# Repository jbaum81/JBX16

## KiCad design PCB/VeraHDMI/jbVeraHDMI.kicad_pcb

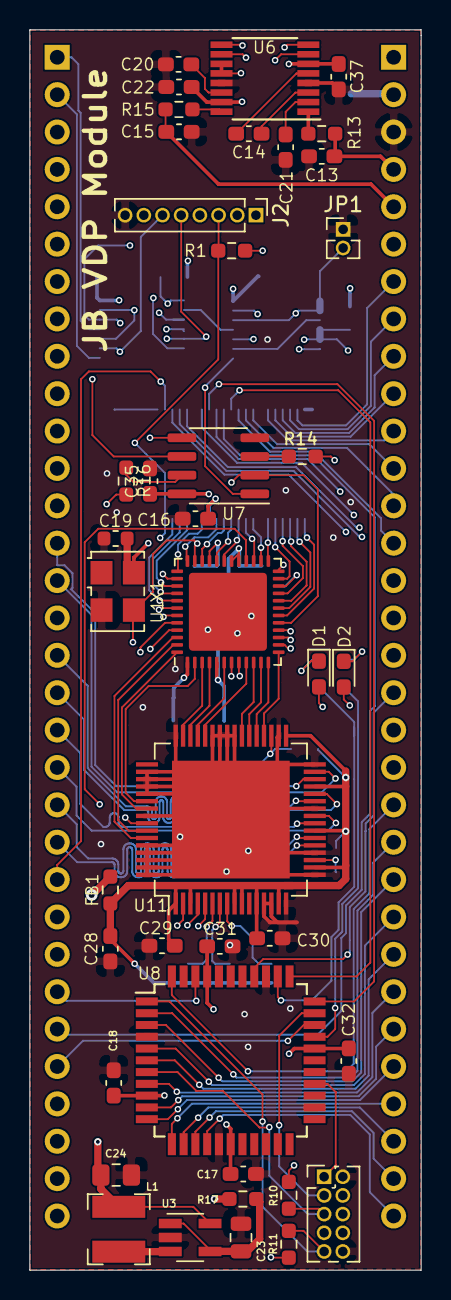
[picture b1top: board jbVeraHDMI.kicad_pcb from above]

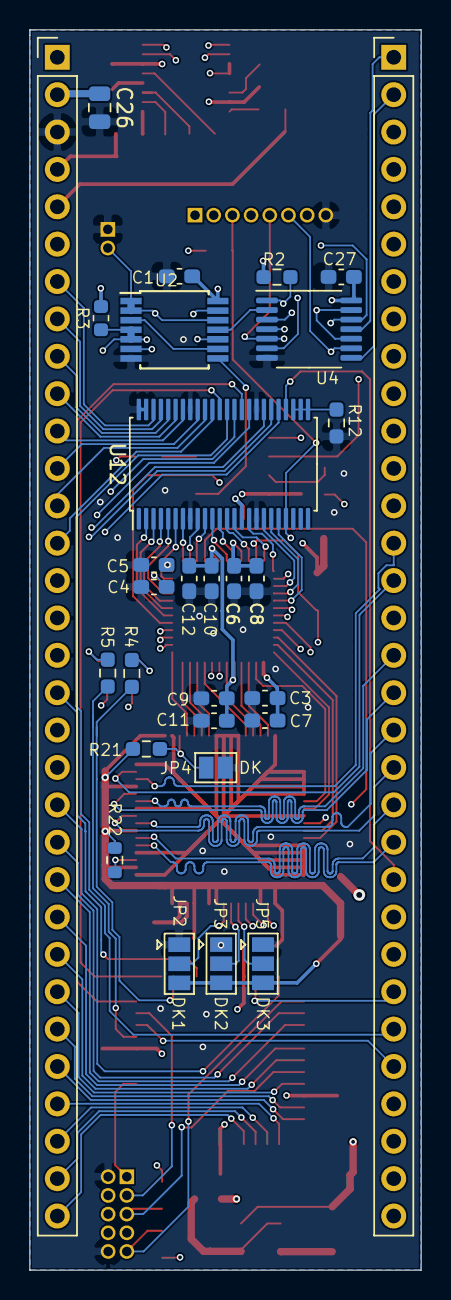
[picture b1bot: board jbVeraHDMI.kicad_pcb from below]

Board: 4 copper layers, 26.6 x 84.3 mm, 70 parts (29 on the bottom side), 119 nets.

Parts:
C1, C3, C4, C5, C6, C9, C10, C16, C17, C18, C27, C31, C32, C35: 100nF; C_0603_1608Metric_Pad1.08x0.95mm_HandSolder
C7, C8, C11, C12, C22, C37: 4.7uF; C_0603_1608Metric_Pad1.08x0.95mm_HandSolder
C13, C15: 2.7nF; C_0603_1608Metric_Pad1.08x0.95mm_HandSolder
C14: 1u; C_0603_1608Metric_Pad1.08x0.95mm_HandSolder
C19: 100nF; C_0603_1608Metric
C20: 2.2uF; C_0603_1608Metric_Pad1.08x0.95mm_HandSolder
C21: 1uF; C_0603_1608Metric_Pad1.08x0.95mm_HandSolder
C23, C26: 10uF; C_0805_2012Metric
C24: 10uF; C_0805_2012Metric_Pad1.18x1.45mm_HandSolder
C28: 10uF; C_0603_1608Metric_Pad1.08x0.95mm_HandSolder
C29, C30: .1uF; C_0603_1608Metric_Pad1.08x0.95mm_HandSolder
D1: RED; LED_0603_1608Metric_Pad1.05x0.95mm_HandSolder
D2: GREEN; LED_0603_1608Metric_Pad1.05x0.95mm_HandSolder
FB1: 600R; R_0603_1608Metric_Pad0.98x0.95mm_HandSolder
J2: Prog; PinHeader_1x08_P1.27mm_Vertical
J4: MercuryII-L; PinHeader_1x32_P2.54mm_Vertical
J5: MercuryII-R; PinHeader_1x32_P2.54mm_Vertical
J7: JTAG; PinHeader_2x05_P1.27mm_Vertical
JP1: Flash enable; PinHeader_1x02_P1.27mm_Vertical
JP2: DK1; SolderJumper-3_P1.3mm_Open_Pad1.0x1.5mm
JP3: DK2; SolderJumper-3_P1.3mm_Open_Pad1.0x1.5mm
JP4: DK; SolderJumper-2_P1.3mm_Open_Pad1.0x1.5mm
JP5: DK3; SolderJumper-3_P1.3mm_Open_Pad1.0x1.5mm
L1: NRS4018T2R2MDGJ; L_Bourns-SRN4018
R1, R2: 10k; R_0603_1608Metric_Pad0.98x0.95mm_HandSolder
R3: 10k; R_0603_1608Metric
R4, R5: 1K; R_0603_1608Metric_Pad0.98x0.95mm_HandSolder
R10, R11, R12, R21: 10K; R_0603_1608Metric_Pad0.98x0.95mm_HandSolder
R13, R15: 560; R_0603_1608Metric_Pad0.98x0.95mm_HandSolder
R14, R16: 47k; R_0603_1608Metric_Pad0.98x0.95mm_HandSolder
R17: 1; R_0603_1608Metric_Pad0.98x0.95mm_HandSolder
R22: 500R; R_0603_1608Metric
U1: ICE40UP5K-SG48ITR50; QFN-48-1EP_7x7mm_P0.5mm_EP5.3x5.3mm
U2: 74AHC00PW; TSSOP-14_4.4x5mm_P0.65mm
U3: LTC3406BES5-1.2; SOT-23-5_HandSoldering
U4: 74CBTLV3126PW,118; TSSOP-14_4.4x5mm_P0.65mm
U6: WM8524CGEDT; TSSOP-16_4.4x5mm_P0.65mm
U7: W25Q16JVSNIQ; SOIC-8_3.9x4.9mm_P1.27mm
U8: ATF1502AS-xAx44; TQFP-44_10x10mm_P0.8mm
U11: TFP410PAP; HTQFP-64-1EP_10x10mm_P0.5mm_EP8x8mm
U12: SN74CB3T16210; TSSOP-48_6.1x12.5mm_P0.5mm
X1: SG5032CAN_25.000000M-TJGA3; Oscillator_SMD_SeikoEpson_SG8002LB-4Pin_5.0x3.2mm

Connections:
+1V2: C9.1, C10.1, C11.1, C12.1, C24.1, L1.2, U1.5, U1.29, U1.30, U3.5
+3V3: C1.1, C3.1, C4.1, C5.1, C6.1, C7.1, C8.1, C16.1, C19.1, C22.1, C26.1, C27.1, C35.1, C37.1, FB1.2, J5.2, R1.1, R2.1, R3.1, R14.1, R16.1, U1.1, U1.22, U1.24, U1.33, U2.14, U4.14, U6.6, U6.11, U6.12, U6.15, U7.8, U12.15, X1.4
+5V: C17.1, C18.1, C31.1, C32.1, D1.2, D2.2, J2.1, J5.1, J7.4, R10.1, R11.1, R17.2, U8.9, U8.17, U8.29, U8.41
AUDIO_BCK: U1.38, U6.9
AUDIO_DATA: U1.42, U6.7
AUDIO_LRCK: U1.43, U6.8
BUS_A0: U1.40, U12.19
BUS_A0_5V: J5.15, U12.30
BUS_A1: U1.39, U12.18
BUS_A1_5V: J5.16, U12.31
BUS_A2: U1.37, U12.16
BUS_A2_5V: J5.17, U12.33
BUS_A3: U1.41, U12.20
BUS_A3_5V: J5.20, U12.29
BUS_A4: U1.34, U12.13
BUS_A4_5V: J5.21, U8.44, U12.35
BUS_A5_5V: J5.22, U8.2
BUS_A6_5V: J5.23, U8.3
BUS_A7_5V: J5.24, U8.5
BUS_A8_5V: J5.25, U8.6
BUS_A9_5V: J5.26, U8.8
BUS_A10_5V: J5.27, U8.10
BUS_A11_5V: J5.28, U8.11
BUS_A12_5V: J5.29, U8.12
BUS_A13_5V: J5.30, U8.13
BUS_A14_5V: J5.31, U8.14
BUS_A15_5V: J5.32, U8.15
BUS_D0: U1.27, U12.10
BUS_D0_5V: J5.14, U12.38
BUS_D1: U1.26, U12.9
BUS_D1_5V: J5.13, U12.39
BUS_D2: U1.25, U12.7
BUS_D2_5V: J5.12, U12.40
BUS_D3: U1.23, U12.6
BUS_D3_5V: J5.11, U12.42
BUS_D4: U1.21, U12.5
BUS_D4_5V: J5.10, U12.43
BUS_D5: U1.20, U12.4
BUS_D5_5V: J5.9, U12.44
BUS_D6: U1.19, U12.3
BUS_D6_5V: J5.8, U12.45
BUS_D7: U1.18, U12.2
BUS_D7_5V: J5.7, U12.46
BUS_IRQ#: U1.32, U12.12
BUS_IRQ#_5V: J4.27, U12.36
BUS_RD#: U1.36, U12.14
BUS_RD#_5V: U8.33, U12.34
BUS_RES#_5V: J4.23, U12.28
BUS_RWB_5V: J4.26, U8.42
BUS_WR#: U1.31, U12.11
BUS_WR#_5V: U8.34, U12.37
D0+: J4.20, U11.25
D0-: J4.19, U11.24
D1+: J4.18, U11.28
D1-: J4.17, U11.27
D2+: J4.15, U11.31
D2-: J4.14, U11.30
DATDD: J4.28, U8.31
DVI33: C28.1, C29.1, C30.1, FB1.1, JP2.3, JP3.3, JP5.3, R21.2, R22.1, U11.1, U11.3, U11.9, U11.10, U11.12, U11.15, U11.18, U11.23, U11.29, U11.33
FLASH_SSEL_N: U2.8, U7.1
FPGA_CDONE: J2.2, JP1.2, R2.2, U1.7, U2.1, U2.2, U2.12, U4.1, U4.4, U4.10, U4.13
FPGA_CRESET_B: J2.3, R1.2, U1.8, U12.21
GND: C1.2, C3.2, C4.2, C5.2, C6.2, C7.2, C8.2, C9.2, C10.2, C11.2, C12.2, C13.2, C15.2, C16.2, C17.2, C18.2, C19.2, C20.2, C21.2, C22.2, C23.2, C24.2, C26.2, C27.2, C28.2, C29.2, C30.2, C31.2, C32.2, C35.2, C37.2, J2.8, J5.3, J7.2, J7.10, JP1.1, JP2.1, JP3.1, JP4.2, JP5.1, R12.1, U1.49, U2.7, U3.2, U4.7, U6.4, U6.13, U7.4, U8.4, U8.16, U8.24, U8.36, U11.13, U11.14, U11.16, U11.17, U11.20, U11.26, U11.32, U11.34, U11.40, U11.41, U11.42, U11.43, U11.48, U11.50, U11.51, U11.52, U11.53, U11.56, U11.60, U11.61, U11.62, U11.63, U11.64, U11.65, U12.8, U12.17, U12.32, U12.41, U12.47, U12.48, X1.2
L_AUDIO: C13.1, J5.4, R13.1
unnamed: C14.1, U6.3
unnamed: C14.2, U6.5
unnamed: C20.1, U6.14
unnamed: C21.1, U6.2
unnamed: C23.1, R17.1, U3.1, U3.4
unnamed: D1.1, R4.1
unnamed: D2.1, R5.1
unnamed: JP2.2, U11.8
unnamed: JP3.2, U11.7
unnamed: JP4.1, R21.1, U11.35
unnamed: JP5.2, U11.6
unnamed: L1.1, U3.3
unnamed: R12.2, U12.25, U12.26, U12.27
unnamed: R13.2, U6.1
unnamed: R14.2, U7.3
unnamed: R15.2, U6.16
unnamed: R16.2, U7.7
unnamed: R22.2, U11.19
unnamed: U2.3, U2.9
unnamed: U2.6, U2.10, U2.13
RDLED: R5.2, U8.30
R_AUDIO: C15.1, J5.5, R15.1
SD_MISO: J4.1, U4.11
SD_MOSI: J4.3, U4.6
SD_SCK: J4.2, U4.8
SD_SSEL: J4.4, U4.3
SD_SSEL_N: U2.11, U4.2
SPI_MISO: J2.4, U1.17, U4.12, U7.2
SPI_MOSI: J2.5, U1.14, U4.5, U7.5
SPI_SCK: J2.6, U1.15, U4.9, U7.6
SPI_SSEL_N: J2.7, R3.2, U1.16, U2.4, U2.5
SYSCLK: U1.35, U6.10, U11.57, X1.3
TCK: J7.1, U8.26
TDI: J7.9, R11.2, U8.1
TDO: J7.3, U8.32
TMS: J7.5, R10.2, U8.7
VGA_B0: U1.46, U11.59
VGA_B1: U1.47, U11.58
VGA_B2: U1.48, U11.55
VGA_B3: U1.2, U11.54
VGA_DE: U1.28, U11.2
VGA_G0: U1.3, U11.47
VGA_G1: U1.4, U11.46
VGA_G2: U1.6, U11.45
VGA_G3: U1.9, U11.44
VGA_HSYNC: U1.44, U11.4
VGA_R0: U1.10, U11.39
VGA_R1: U1.11, U11.38
VGA_R2: U1.12, U11.37
VGA_R3: U1.13, U11.36
VGA_VSYNC: U1.45, U11.5
WRLED: R4.2, U8.35
clk+: J4.21, U11.22
clk-: J4.22, U11.21
cpuClk: J5.18, U8.37

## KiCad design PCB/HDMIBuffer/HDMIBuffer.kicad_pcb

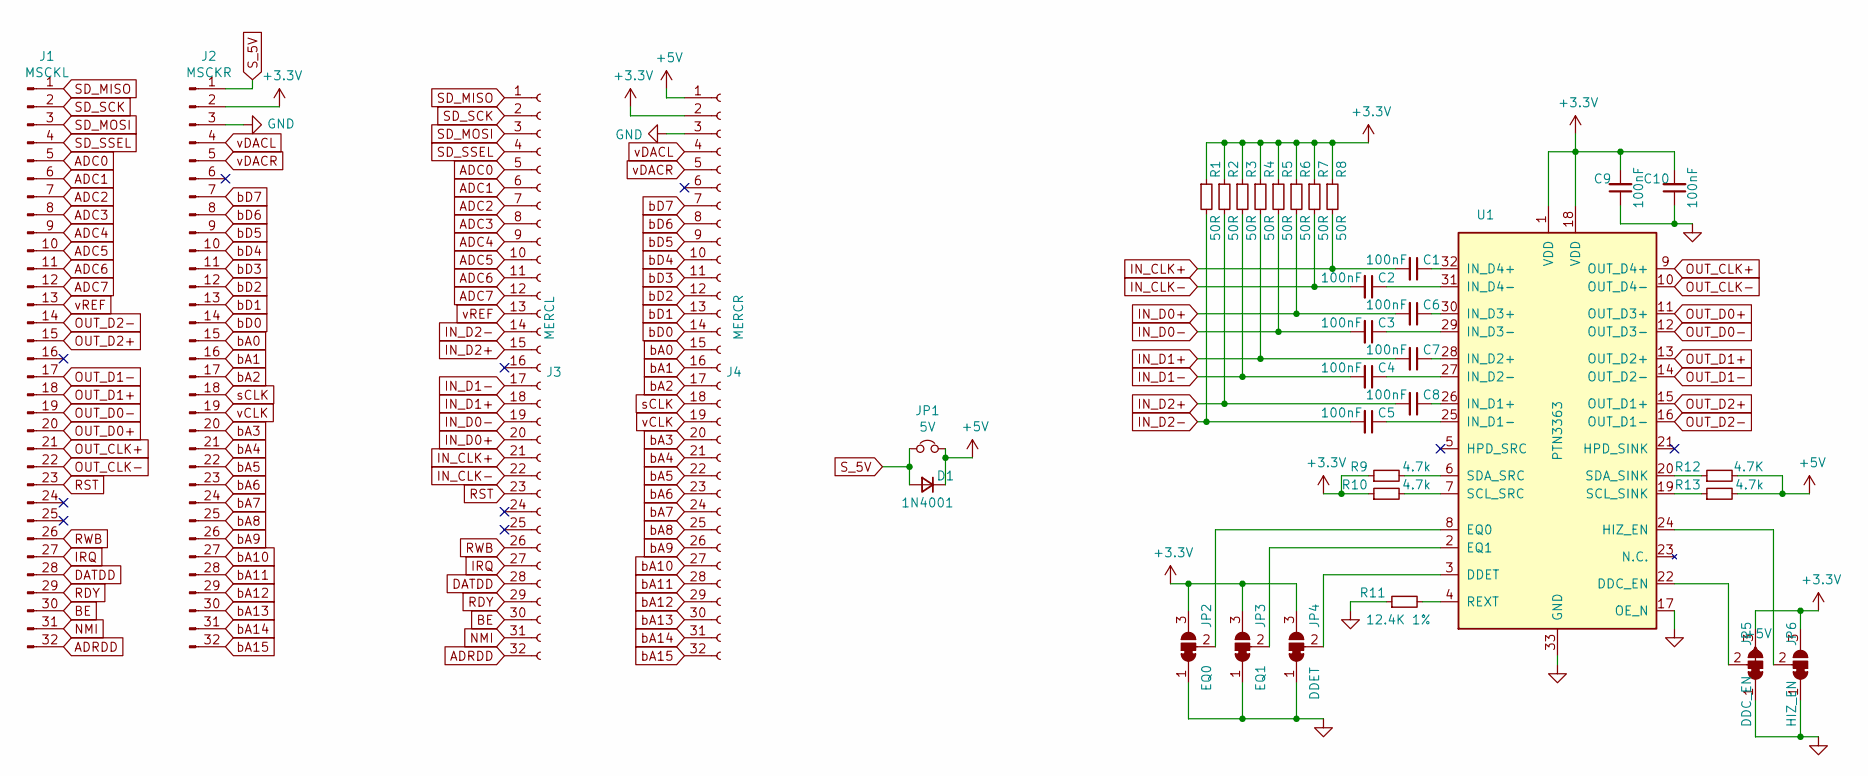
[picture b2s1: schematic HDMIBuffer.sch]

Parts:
C1, C2, C3, C4, C5, C6, C7, C8, C9, C10: 100nF; C_0603_1608Metric_Pad1.08x0.95mm_HandSolder
D1: 1N4001; D_0805_2012Metric
J1: MSCKL; PinHeader_1x32_P2.54mm_Vertical
J2: MSCKR; PinHeader_1x32_P2.54mm_Vertical
J3: MERCL; PinSocket_1x32_P2.54mm_Vertical
J4: MERCR; PinSocket_1x32_P2.54mm_Vertical
JP1: 5V; SolderJumper-2_P1.3mm_Open_Pad1.0x1.5mm
JP2: EQ0; SolderJumper-3_P1.3mm_Bridged12_Pad1.0x1.5mm_NumberLabels
JP3: EQ1; SolderJumper-3_P1.3mm_Bridged12_Pad1.0x1.5mm_NumberLabels
JP4: DDET; SolderJumper-3_P1.3mm_Bridged12_Pad1.0x1.5mm_NumberLabels
JP5: DDC_EN; SolderJumper-3_P1.3mm_Bridged12_Pad1.0x1.5mm_NumberLabels
JP6: HIZ_EN; SolderJumper-3_P1.3mm_Bridged12_Pad1.0x1.5mm_NumberLabels
R1, R2, R3, R4, R5, R6, R7, R8: 50R; R_0603_1608Metric_Pad0.98x0.95mm_HandSolder
R9, R10, R13: 4.7k; R_0603_1608Metric_Pad0.98x0.95mm_HandSolder
R11: 12.4K 1%; R_0603_1608Metric_Pad0.98x0.95mm_HandSolder
R12: 4.7K; R_0603_1608Metric_Pad0.98x0.95mm_HandSolder
U1: PTN3363; TQFN-32-1EP_5x5mm_P0.5mm_EP2.1x2.1mm_ThermalVias

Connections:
+3V3: C9.2, C10.2, J2.2, J4.2, JP2.3 (B), JP3.3 (B), JP4.3 (B), JP5.3 (B), JP6.3 (B), R1.1, R2.1, R3.1, R4.1, R5.1, R6.1, R7.1, R8.1, R9.1, R10.1, U1.1 (VDD), U1.18 (VDD)
+5V: D1.1 (K), J4.1, JP1.2, R12.2, R13.2
ADC0: J1.5, J3.5
ADC1: J1.6, J3.6
ADC2: J1.7, J3.7
ADC3: J1.8, J3.8
ADC4: J1.9, J3.9
ADC5: J1.10, J3.10
ADC6: J1.11, J3.11
ADC7: J1.12, J3.12
ADRDD: J1.32, J3.32
BE: J1.30, J3.30
DATDD: J1.28, J3.28
GND: C9.1, C10.1, J2.3, J4.3, JP2.1 (A), JP3.1 (A), JP4.1 (A), JP5.1 (A), JP6.1 (A), R11.1, U1.17 (OE_N), U1.33 (GND)
IN_CLK+: C1.2, J3.21, R8.2
IN_CLK-: C2.2, J3.22, R7.2
IN_D0+: C6.2, J3.20, R6.2
IN_D0-: C3.2, J3.19, R5.2
IN_D1+: C7.2, J3.18, R4.2
IN_D1-: C4.2, J3.17, R3.2
IN_D2+: C8.2, J3.15, R2.2
IN_D2-: C5.2, J3.14, R1.2
IRQ: J1.27, J3.27
NMI: J1.31, J3.31
unnamed: C1.1, U1.32 (IN_D4+)
unnamed: C2.1, U1.31 (IN_D4-)
unnamed: C3.1, U1.29 (IN_D3-)
unnamed: C4.1, U1.27 (IN_D2-)
unnamed: C5.1, U1.25 (IN_D1-)
unnamed: C6.1, U1.30 (IN_D3+)
unnamed: C7.1, U1.28 (IN_D2+)
unnamed: C8.1, U1.26 (IN_D1+)
unnamed: JP2.2 (C), U1.8 (EQ0)
unnamed: JP3.2 (C), U1.2 (EQ1)
unnamed: JP4.2 (C), U1.3 (DDET)
unnamed: JP5.2 (C), U1.22 (DDC_EN)
unnamed: JP6.2 (C), U1.24 (HIZ_EN)
unnamed: R9.2, U1.6 (SDA_SRC)
unnamed: R10.2, U1.7 (SCL_SRC)
unnamed: R11.2, U1.4 (REXT)
unnamed: R12.1, U1.20 (SDA_SINK)
unnamed: R13.1, U1.19 (SCL_SINK)
OUT_CLK+: J1.21, U1.9 (OUT_D4+)
OUT_CLK-: J1.22, U1.10 (OUT_D4-)
OUT_D0+: J1.20, U1.11 (OUT_D3+)
OUT_D0-: J1.19, U1.12 (OUT_D3-)
OUT_D1+: J1.18, U1.13 (OUT_D2+)
OUT_D1-: J1.17, U1.14 (OUT_D2-)
OUT_D2+: J1.15, U1.15 (OUT_D1+)
OUT_D2-: J1.14, U1.16 (OUT_D1-)
RDY: J1.29, J3.29
RST: J1.23, J3.23
RWB: J1.26, J3.26
SD_MISO: J1.1, J3.1
SD_MOSI: J1.3, J3.3
SD_SCK: J1.2, J3.2
SD_SSEL: J1.4, J3.4
S_5V: D1.2 (A), J2.1, JP1.1
bA0: J2.15, J4.15
bA1: J2.16, J4.16
bA2: J2.17, J4.17
bA3: J2.20, J4.20
bA4: J2.21, J4.21
bA5: J2.22, J4.22
bA6: J2.23, J4.23
bA7: J2.24, J4.24
bA8: J2.25, J4.25
bA9: J2.26, J4.26
bA10: J2.27, J4.27
bA11: J2.28, J4.28
bA12: J2.29, J4.29
bA13: J2.30, J4.30
bA14: J2.31, J4.31
bA15: J2.32, J4.32
bD0: J2.14, J4.14
bD1: J2.13, J4.13
bD2: J2.12, J4.12
bD3: J2.11, J4.11
bD4: J2.10, J4.10
bD5: J2.9, J4.9
bD6: J2.8, J4.8
bD7: J2.7, J4.7
sCLK: J2.18, J4.18
vCLK: J2.19, J4.19
vDACL: J2.4, J4.4
vDACR: J2.5, J4.5
vREF: J1.13, J3.13

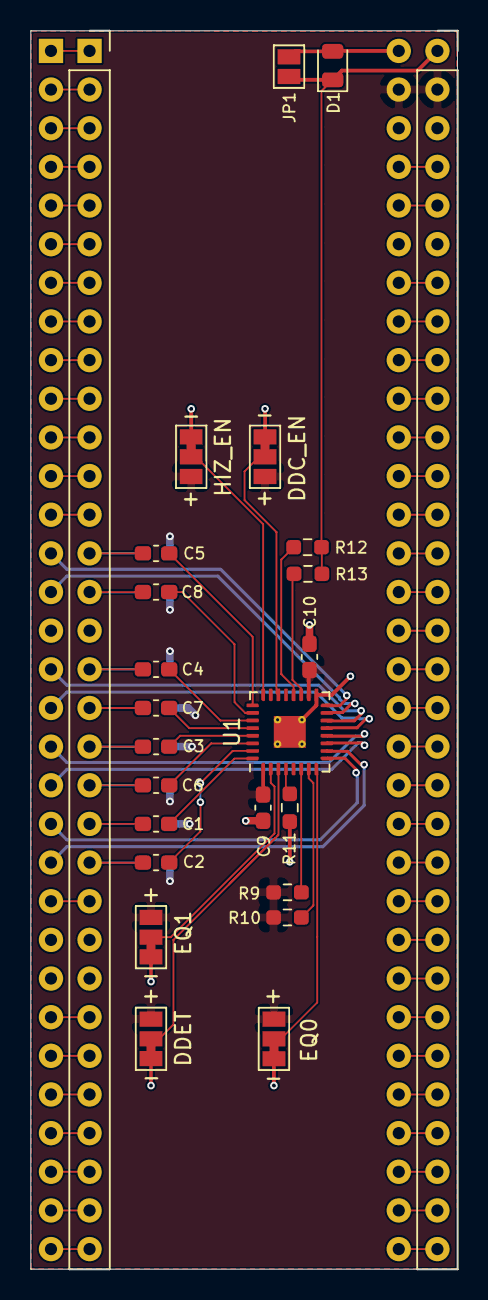
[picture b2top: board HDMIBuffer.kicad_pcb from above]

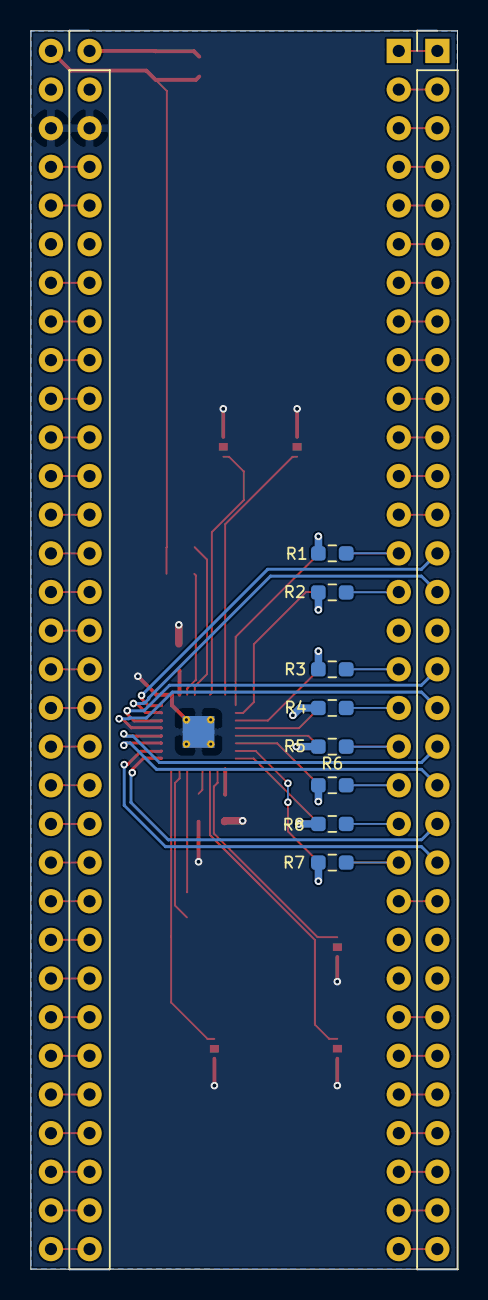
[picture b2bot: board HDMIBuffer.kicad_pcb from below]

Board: 2 copper layers, 28.0 x 81.4 mm, 35 parts (10 on the bottom side), 87 nets.

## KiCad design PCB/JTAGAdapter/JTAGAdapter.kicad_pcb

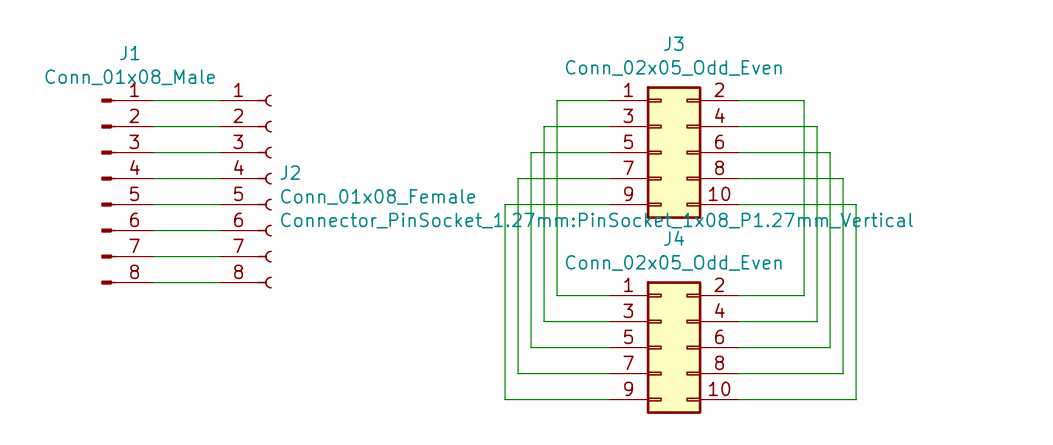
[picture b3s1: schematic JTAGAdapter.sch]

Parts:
J1: Conn_01x08_Male; PinHeader_1x08_P2.54mm_Horizontal
J2: Conn_01x08_Female; PinSocket_1x08_P1.27mm_Vertical
J3: Conn_02x05_Odd_Even; PinHeader_2x05_P2.54mm_Horizontal
J4: Conn_02x05_Odd_Even; PinSocket_2x05_P1.27mm_Horizontal

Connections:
unnamed: J1.1, J2.1
unnamed: J1.2, J2.2
unnamed: J1.3, J2.3
unnamed: J1.4, J2.4
unnamed: J1.5, J2.5
unnamed: J1.6, J2.6
unnamed: J1.7, J2.7
unnamed: J1.8, J2.8
unnamed: J3.1, J4.1
unnamed: J3.2, J4.2
unnamed: J3.3, J4.3
unnamed: J3.4, J4.4
unnamed: J3.5, J4.5
unnamed: J3.6, J4.6
unnamed: J3.7, J4.7
unnamed: J3.8, J4.8
unnamed: J3.9, J4.9
unnamed: J3.10, J4.10

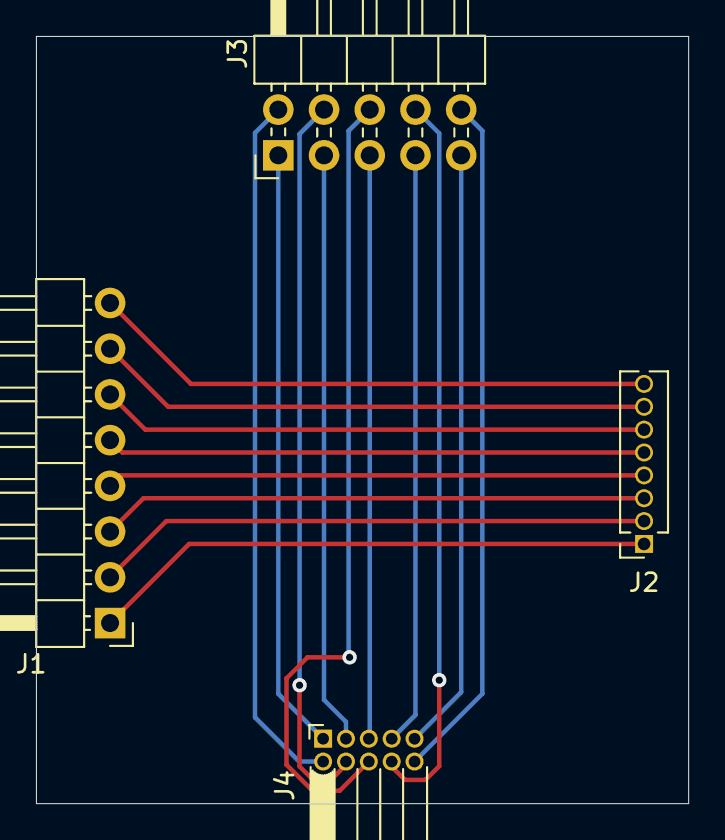
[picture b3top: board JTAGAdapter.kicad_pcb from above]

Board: 2 copper layers, 36.2 x 42.6 mm, 4 parts (0 on the bottom side), 18 nets.

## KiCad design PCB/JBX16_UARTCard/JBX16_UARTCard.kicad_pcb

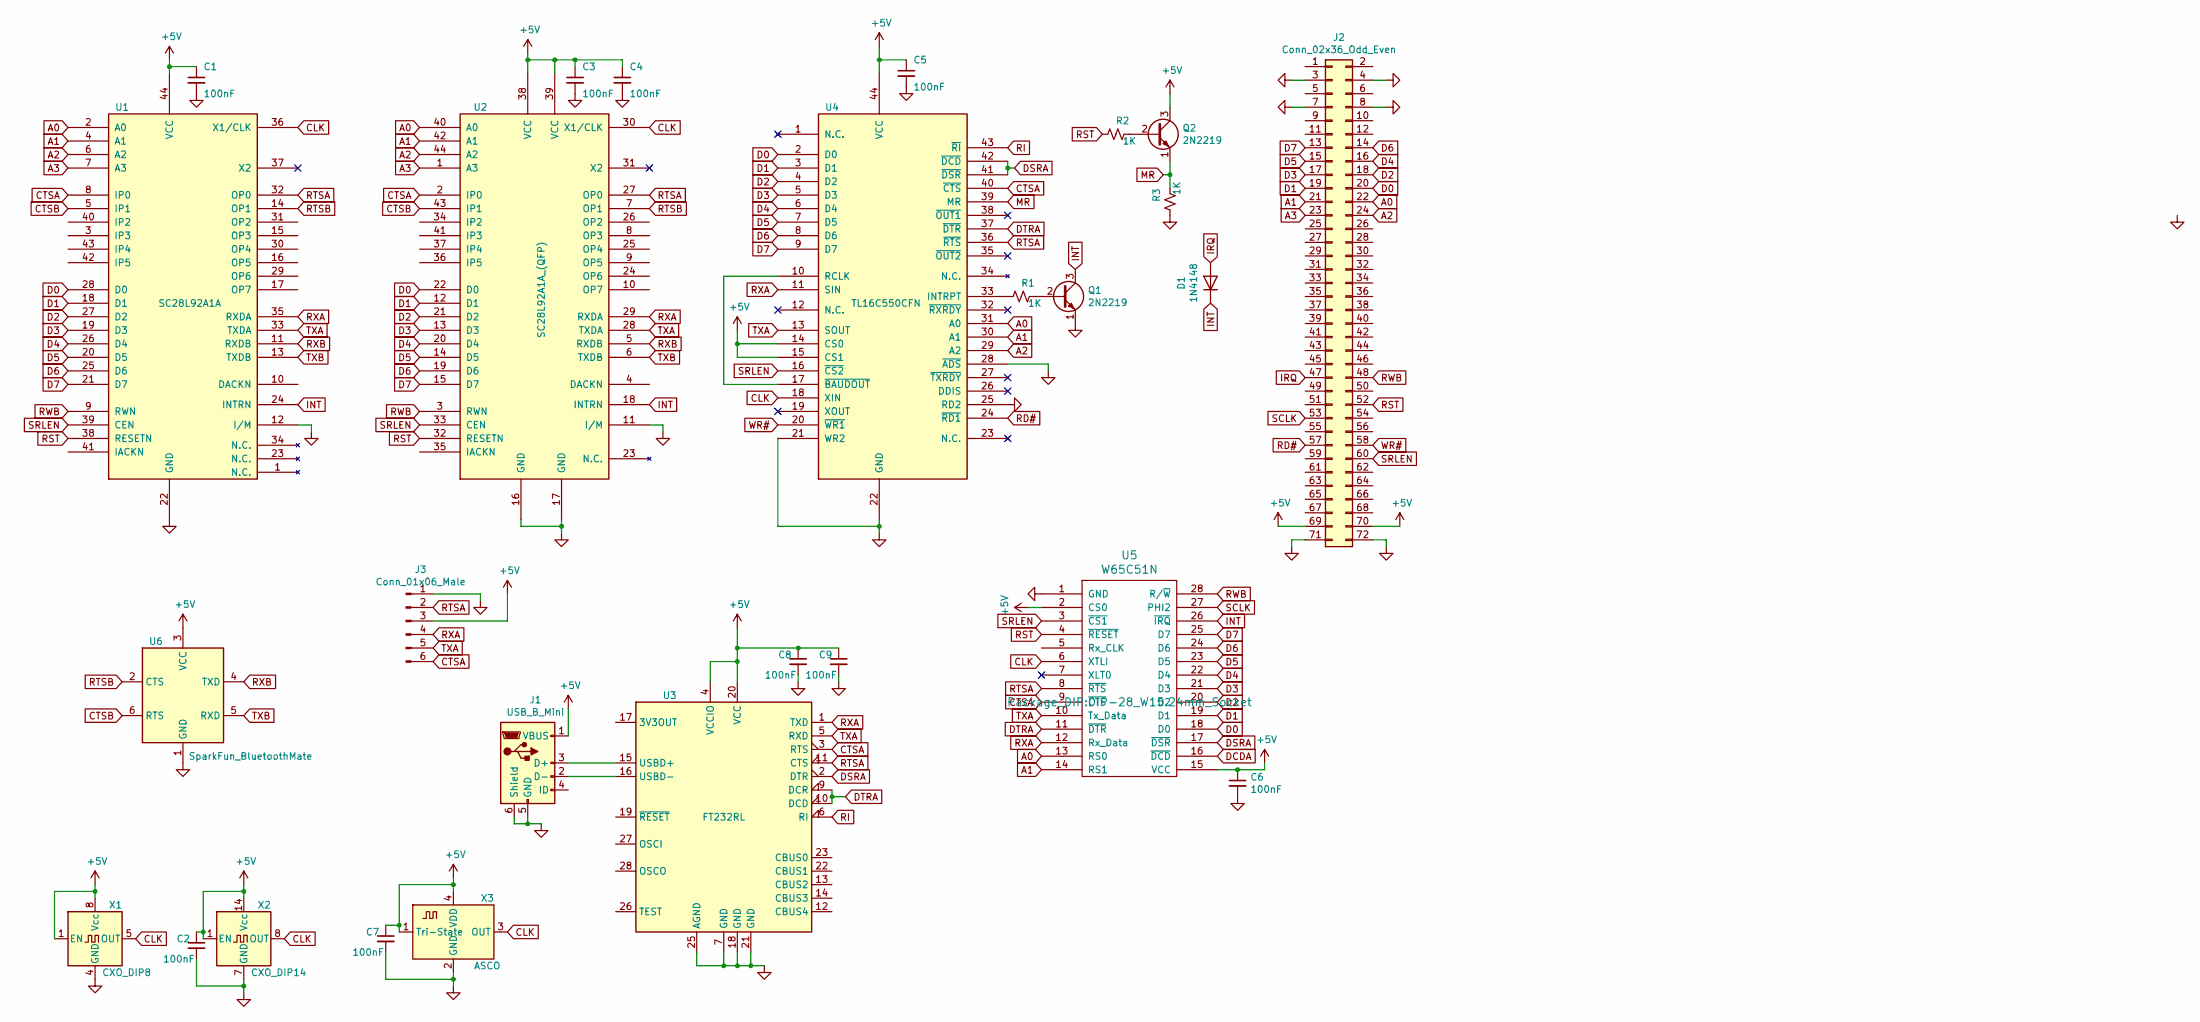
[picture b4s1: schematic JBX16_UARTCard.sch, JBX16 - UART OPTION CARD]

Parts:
C1, C2, C3, C4, C5, C6: 100nF; C_Disc_D3.0mm_W1.6mm_P2.50mm
C7, C8, C9: 100nF; C_0603_1608Metric_Pad1.08x0.95mm_HandSolder
D1: 1N4148; D_T-1_P5.08mm_Horizontal
J1: USB_B_Mini; USB_Mini-B_Wuerth_65100516121_Horizontal
J2: Conn_02x36_Odd_Even; PinHeader_2x36_P2.54mm_Horizontal
J3: Conn_01x06_Male; PinHeader_1x06_P2.54mm_Horizontal
Q1, Q2: 2N2219; TO-92
R1, R2, R3: 1K; R_Axial_DIN0204_L3.6mm_D1.6mm_P5.08mm_Horizontal
U1: SC28L92A1A; PLCC-44_THT-Socket
U2: SC28L92A1A_(QFP); PQFP-44_10x10mm_P0.8mm
U3: FT232RL; SSOP-28_5.3x10.2mm_P0.65mm
U4: TL16C550CFN; PLCC-44_THT-Socket
U5: W65C51N; DIP-28_W15.24mm_Socket
U6: SparkFun_BluetoothMate
X1: CXO_DIP8; Oscillator_DIP-8
X2: CXO_DIP14; Oscillator_DIP-14
X3: ASCO; Oscillator_SMD_EuroQuartz_XO91-4Pin_7.0x5.0mm_HandSoldering

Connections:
+5V: C1.1, C2.1, C3.1, C4.1, C5.1, C6.1, C7.1, C8.1, C9.1, J1.1 (VBUS), J2.69, J2.70, J3.3, Q2.3 (C), U1.44 (VCC), U2.38 (VCC), U2.39 (VCC), U3.4 (VCCIO), U3.20 (VCC), U4.14 (CS0), U4.15 (CS1), U4.44 (VCC), U5.2 (CS0), U5.15 (VCC), U6.3 (VCC), X1.1 (EN), X1.8 (Vcc), X2.1 (EN), X2.14 (Vcc), X3.1 (Tri-State), X3.4 (VDD)
A0: J2.22, U1.2 (A0), U2.40 (A0), U4.31 (A0), U5.13 (RS0)
A1: J2.21, U1.4 (A1), U2.42 (A1), U4.30 (A1), U5.14 (RS1)
A2: J2.24, U1.6 (A2), U2.44 (A2), U4.29 (A2)
A3: J2.23, U1.7 (A3), U2.1 (A3)
CLK: U1.36 (X1/CLK), U2.30 (X1/CLK), U4.18 (XIN), U5.6 (XTLI), X1.5 (OUT), X2.8 (OUT), X3.3 (OUT)
CTSA: J3.6, U1.8 (IP0), U2.2 (IP0), U3.3 (RTS), U4.40 (~CTS), U5.9 (~CTS)
CTSB: U1.5 (IP1), U2.43 (IP1), U6.6 (RTS)
D0: J2.20, U1.28 (D0), U2.22 (D0), U4.2 (D0), U5.18 (D0)
D1: J2.19, U1.18 (D1), U2.12 (D1), U4.3 (D1), U5.19 (D1)
D2: J2.18, U1.27 (D2), U2.21 (D2), U4.4 (D2), U5.20 (D2)
D3: J2.17, U1.19 (D3), U2.13 (D3), U4.5 (D3), U5.21 (D3)
D4: J2.16, U1.26 (D4), U2.20 (D4), U4.6 (D4), U5.22 (D4)
D5: J2.15, U1.20 (D5), U2.14 (D5), U4.7 (D5), U5.23 (D5)
D6: J2.14, U1.25 (D6), U2.19 (D6), U4.8 (D6), U5.24 (D6)
D7: J2.13, U1.21 (D7), U2.15 (D7), U4.9 (D7), U5.25 (D7)
DSRA: U3.2 (DTR), U4.41 (~DSR), U4.42 (~DCD), U5.17 (~DSR)
DTRA: U3.9 (DCR), U3.10 (DCD), U4.37 (~DTR), U5.11 (~DTR)
GND: C1.2, C2.2, C3.2, C4.2, C5.2, C6.2, C7.2, C8.2, C9.2, J1.5 (GND), J1.6 (Shield), J2.3, J2.4, J2.7, J2.8, J2.71, J2.72, J3.1, Q1.1 (E), R3.2, U1.12 (I/M), U1.22 (GND), U2.11 (I/M), U2.16 (GND), U2.17 (GND), U3.7 (GND), U3.18 (GND), U3.21 (GND), U3.25 (AGND), U4.21 (WR2), U4.22 (GND), U4.25 (RD2), U4.28 (~ADS), U5.1 (GND), U6.1 (GND), X1.4 (GND), X2.7 (GND), X3.2 (GND)
INT: D1.1 (K), Q1.3 (C), U1.24 (INTRN), U2.18 (INTRN), U5.26 (~IRQ)
IRQ: D1.2 (A), J2.47
MR: Q2.1 (E), R3.1, U4.39 (MR)
unnamed: J1.2 (D-), U3.16 (USBD-)
unnamed: J1.3 (D+), U3.15 (USBD+)
unnamed: Q1.2 (B), R1.1
unnamed: Q2.2 (B), R2.1
unnamed: R1.2, U4.33 (INTRPT)
unnamed: U4.10 (RCLK), U4.17 (~BAUDOUT)
RD#: J2.57, U4.24 (~RD1)
RI: U3.6 (RI), U4.43 (~RI)
RST: J2.52, R2.2, U1.38 (RESETN), U2.32 (RESETN), U5.4 (~RESET)
RTSA: J3.2, U1.32 (OP0), U2.27 (OP0), U3.11 (CTS), U4.36 (~RTS), U5.8 (~RTS)
RTSB: U1.14 (OP1), U2.7 (OP1), U6.2 (CTS)
RWB: J2.48, U1.9 (RWN), U2.3 (RWN), U5.28 (R/~W)
RXA: J3.4, U1.35 (RXDA), U2.29 (RXDA), U3.1 (TXD), U4.11 (SIN), U5.12 (Rx_Data)
RXB: U1.11 (RXDB), U2.5 (RXDB), U6.4 (TXD)
SCLK: J2.53, U5.27 (PHI2)
SRLEN: J2.60, U1.39 (CEN), U2.33 (CEN), U4.16 (~CS2), U5.3 (~CS1)
TXA: J3.5, U1.33 (TXDA), U2.28 (TXDA), U3.5 (RXD), U4.13 (SOUT), U5.10 (Tx_Data)
TXB: U1.13 (TXDB), U2.6 (TXDB), U6.5 (RXD)
WR#: J2.58, U4.20 (~WR1)

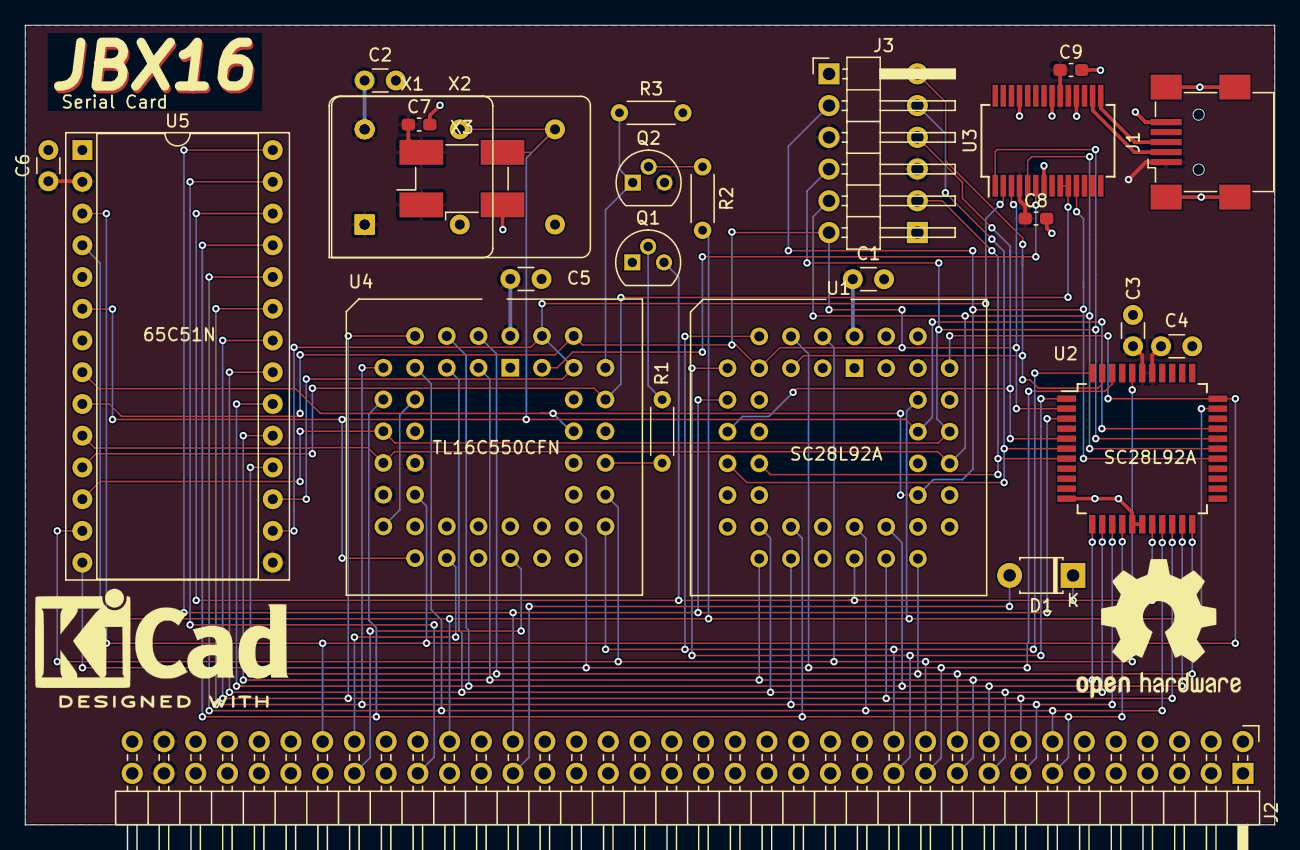
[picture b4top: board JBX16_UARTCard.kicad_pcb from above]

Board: 2 copper layers, 100.0 x 64.0 mm, 27 parts (1 on the bottom side), 41 nets.

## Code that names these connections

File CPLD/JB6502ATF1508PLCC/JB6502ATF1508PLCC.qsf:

# -------------------------------------------------------------------------- #
#
# Copyright (C) 1991-2013 Altera Corporation
# Your use of Altera Corporation's design tools, logic functions 
# and other software and tools, and its AMPP partner logic 
# functions, and any output files from any of the foregoing 
# (including device programming or simulation files), and any 
# associated documentation or information are expressly subject 
# to the terms and conditions of the Altera Program License 
# Subscription Agreement, Altera MegaCore Function License 
# Agreement, or other applicable license agreement, including, 
# without limitation, that your use is for the sole purpose of 
# programming logic devices manufactured by Altera and sold by 
# Altera or its authorized distributors.  Please refer to the 
# applicable agreement for further details.
#
# -------------------------------------------------------------------------- #
#
# Quartus II 64-Bit
# Version 13.0.1 Build 232 06/12/2013 Service Pack 1 SJ Web Edition
# Date created = 15:21:08  May 06, 2022
#
# -------------------------------------------------------------------------- #
#
# Notes:
#
# 1) The default values for assignments are stored in the file:
#		JB6502ATF1508PLCC_assignment_defaults.qdf
#    If this file doesn't exist, see file:
#		assignment_defaults.qdf
#
# 2) Altera recommends that you do not modify this file. This
#    file is updated automatically by the Quartus II software
#    and any changes you make may be lost or overwritten.
#
# -------------------------------------------------------------------------- #


set_global_assignment -name FAMILY MAX7000S
set_global_assignment -name DEVICE "EPM7128SLC84-10"
set_global_assignment -name TOP_LEVEL_ENTITY JB6502ATF1508PLCC
set_global_assignment -name ORIGINAL_QUARTUS_VERSION "13.0 SP1"
set_global_assignment -name PROJECT_CREATION_TIME_DATE "15:21:08  MAY 06, 2022"
set_global_assignment -name LAST_QUARTUS_VERSION "13.0 SP1"
set_global_assignment -name PROJECT_OUTPUT_DIRECTORY output_files
set_global_assignment -name ERROR_CHECK_FREQUENCY_DIVISOR "-1"
set_global_assignment -name VERILOG_FILE JB6502ATF1508PLCC.v
set_global_assignment -name MAX7000_DEVICE_IO_STANDARD TTL
set_location_assignment PIN_44 -to adrBusLo[0]
set_location_assignment PIN_45 -to adrBusLo[1]
set_location_assignment PIN_46 -to adrBusLo[2]
set_location_assignment PIN_48 -to adrBusLo[3]
set_location_assignment PIN_49 -to adrBusLo[4]
set_location_assignment PIN_50 -to adrBusLo[5]
set_location_assignment PIN_51 -to adrBusLo[6]
set_location_assignment PIN_52 -to adrBusLo[7]
set_location_assignment PIN_15 -to datBus[0]
set_location_assignment PIN_16 -to datBus[1]
set_location_assignment PIN_24 -to datBus[2]
set_location_assignment PIN_25 -to datBus[3]
set_location_assignment PIN_54 -to datBus[4]
set_location_assignment PIN_55 -to datBus[5]
set_location_assignment PIN_63 -to datBus[6]
set_location_assignment PIN_64 -to datBus[7]
set_location_assignment PIN_1 -to rst
set_location_assignment PIN_83 -to clk
set_location_assignment PIN_84 -to oe
set_location_assignment PIN_2 -to rw
set_location_assignment PIN_31 -to v0En
set_location_assignment PIN_30 -to roEn
set_location_assignment PIN_28 -to raEn
set_location_assignment PIN_17 -to hr0En
set_location_assignment PIN_18 -to hr1En
set_location_assignment PIN_20 -to hr2En
set_location_assignment PIN_22 -to clkWr
set_location_assignment PIN_27 -to hr3En
set_location_assignment PIN_29 -to oeLow
set_location_assignment PIN_21 -to datDD
set_location_assignment PIN_68 -to ioEn
set_location_assignment PIN_67 -to srlEn
set_location_assignment PIN_65 -to v1En
set_location_assignment PIN_40 -to adrBusHi[0]
set_location_assignment PIN_36 -to adrBusHi[1]
set_location_assignment PIN_35 -to adrBusHi[2]
set_location_assignment PIN_34 -to adrBusHi[3]
set_location_assignment PIN_33 -to adrBusHi[4]
set_location_assignment PIN_37 -to adrBusHi[5]
set_location_assignment PIN_39 -to adrBusHi[6]
set_location_assignment PIN_41 -to adrBusHi[7]
set_location_assignment PIN_12 -to adrBanks[0]
set_location_assignment PIN_11 -to adrBanks[1]
set_location_assignment PIN_10 -to adrBanks[2]
set_location_assignment PIN_9 -to adrBanks[3]
set_location_assignment PIN_8 -to adrBanks[4]
set_location_assignment PIN_6 -to adrBanks[5]
set_location_assignment PIN_5 -to adrBanks[6]
set_location_assignment PIN_4 -to adrBanks[7]
set_location_assignment PIN_70 -to sysClk
set_location_assignment PIN_69 -to viaClk
set_location_assignment PIN_77 -to ymfEn
set_location_assignment PIN_80 -to activity
set_global_assignment -name ALLOW_POWER_UP_DONT_CARE ON
set_global_assignment -name SYNTH_TIMING_DRIVEN_SYNTHESIS OFF
set_global_assignment -name OPTIMIZE_HOLD_TIMING OFF
set_global_assignment -name OPTIMIZE_MULTI_CORNER_TIMING OFF
set_global_assignment -name FITTER_EFFORT "STANDARD FIT"
set_location_assignment PIN_74 -to vpp

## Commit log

2022-07-23 Work In Progress
    Initial Commit
2022-07-23 Sharing CPLD code
2022-07-24 Updates to layout
2022-07-29 Many Updates
2022-07-30 Updated CPLD project for Vera HDMI
2022-07-30 Adding Vera HDMI PCB
    Vera HDMI for Mercury II FPGA socket.
2022-07-30 Board build progress.
2022-08-23 CPLD Code Updates
2022-08-23 Final Changes, PCB's ordered
2022-08-23 JBX16 UART Card Addition
2022-08-23 2.5mm to 1.25mm adapter board
2022-08-23 Vera HDMI final updates, PCB's ordered.
2022-08-25 Fixed banking to include static assignment to 0 for low ram. Code tests good.
2022-08-26 CPLD Updates
2022-08-26 Fixed Resistor reference misalignment
2022-08-27 Publish Vera HDMI Card
2022-09-02 Slowed clock stretch to 2mhz
2022-09-14 Notated bad circuits
    5v rail leaking into RST bus through Q1, needs revision.
    ATX Loading during power down is trash, do not use R39,R40,Q5,Q6
2022-10-02 ATX Loading + RST FET + Activity FET
    Removed ATX load circuit. Updated RST + Activity LED drivers from BJT to P-FET.
2022-10-02 Re-Enabled Serial En line.
2022-10-21 Fix for Max7000 CPLD
    Introduced power on delay before letting the vclock and sclock run.
2023-05-22 Remove HDMI Buffer Kicad files
2023-05-22 Remove x16 board backup files
2023-05-22 Remove UART Card
2023-05-22 Remove old X16 SMD board and backup files.
2023-05-22 remove files
2023-05-22 JBx16 board update
2023-08-25 backups
2023-10-26 PLCC Update for VP Fix
